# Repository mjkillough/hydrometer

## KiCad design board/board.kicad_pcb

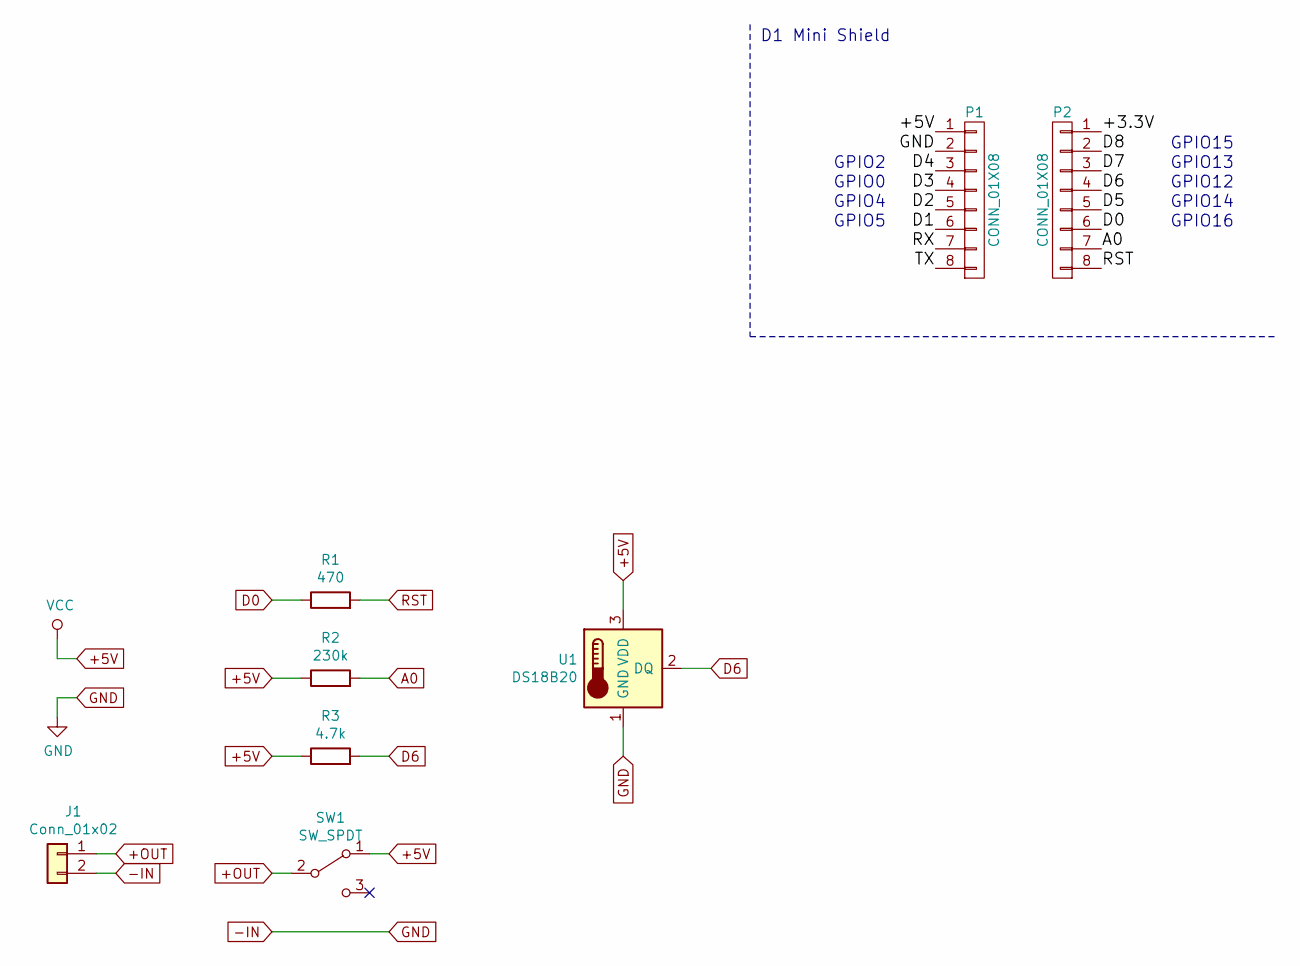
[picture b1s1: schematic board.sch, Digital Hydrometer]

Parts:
J1: Conn_01x02; PinHeader_1x02_P2.54mm_Vertical
P1, P2: CONN_01X08; D1_mini_Pin_Header
R1: 470; R_Axial_DIN0411_L9.9mm_D3.6mm_P12.70mm_Horizontal
R2: 230k; R_Axial_DIN0411_L9.9mm_D3.6mm_P12.70mm_Horizontal
R3: 4.7k; R_Axial_DIN0411_L9.9mm_D3.6mm_P12.70mm_Horizontal
SW1: SW_SPDT; SS-12F23-SPDT
U1: DS18B20; TO-92_Inline

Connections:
+5V: P1.1, R2.1, R3.1, SW1.1 (A), U1.3 (VDD)
+OUT: J1.1, SW1.2 (B)
-IN: J1.2, P1.2, U1.1 (GND)
/+3.3V: P2.1
/D1: P1.6
/D2: P1.5
/D3: P1.4
/D4: P1.3
/D5: P2.5
/D7: P2.3
/D8: P2.2
/RX: P1.7
/TX: P1.8
A0: P2.7, R2.2
D0: P2.6, R1.1
D6: P2.4, R3.2, U1.2 (DQ)
RST: P2.8, R1.2

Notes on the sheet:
GPIO2
GPIO0
GPIO4
GPIO5
GPIO15
GPIO13
GPIO12
GPIO14
GPIO16
D1 Mini Shield

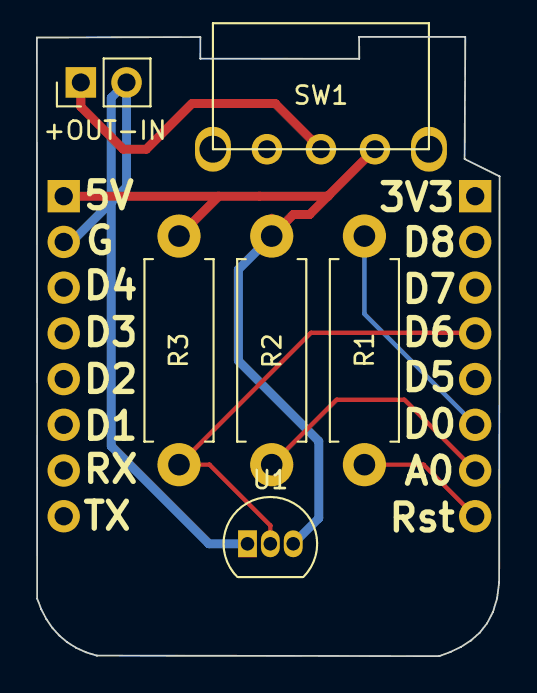
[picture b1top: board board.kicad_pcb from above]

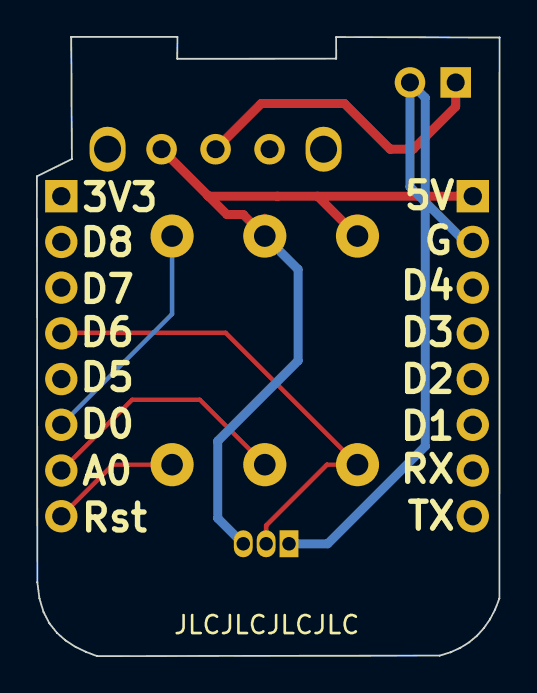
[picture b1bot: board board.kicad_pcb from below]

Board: 2 copper layers, 25.7 x 34.4 mm, 8 parts (2 on the bottom side), 7 nets.

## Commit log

2020-07-12 Add Sled model.
2020-10-29 kicad
2020-10-29 updated kicad
    from ages ago - I think it switches to using a hat template for the d1
    mini.
2020-10-29 Add cache.lib.
    This apparantly contains all components in the project, so that it can
    be modified on PCs with a different KiCad library.
2020-10-29 Add -rescue.{lib,dcm}.
2020-10-29 Add footprint for SS-12F23 switch.
2020-10-29 Add footprint caches for project.
2020-10-29 Add docs/ folder.
2020-10-31 Switch SW1 footprint for actual part.
2020-10-31 Add .gitignore.
2020-10-31 Add JLCJLCJLCJLC to silk screen.
    ... to make sure JLCPCB place the order number somewhere hidden.
2020-11-01 Tweak schematic layout.
2020-11-01 Prepare to generate gerber.
2020-11-01 Add gerbers.
    I've decided to commit this so that I can track exactly what I sent to
    be fabricated at each step.
2020-11-22 firmware: initial blinky
2020-11-23 firmware: read accelerometer data
2020-11-23 firmware: measure angle with mpu
2020-11-23 firmware: make HTTP requests
2020-11-23 firmware: circular buffer for measurements
2020-11-23 server: initial debug server
2020-11-23 firmware: post measurements in batches
2020-11-23 firmware: split out measurements buffering
2020-11-23 firmware: clean-up main
2020-11-23 firmware: rename task to loop
2020-11-23 firmware: send temp
2020-11-23 server: accept temp
2020-11-23 firmware: send timestamp with measurement
2020-11-23 server: accept timestamp
2020-11-23 server: return timestamp
